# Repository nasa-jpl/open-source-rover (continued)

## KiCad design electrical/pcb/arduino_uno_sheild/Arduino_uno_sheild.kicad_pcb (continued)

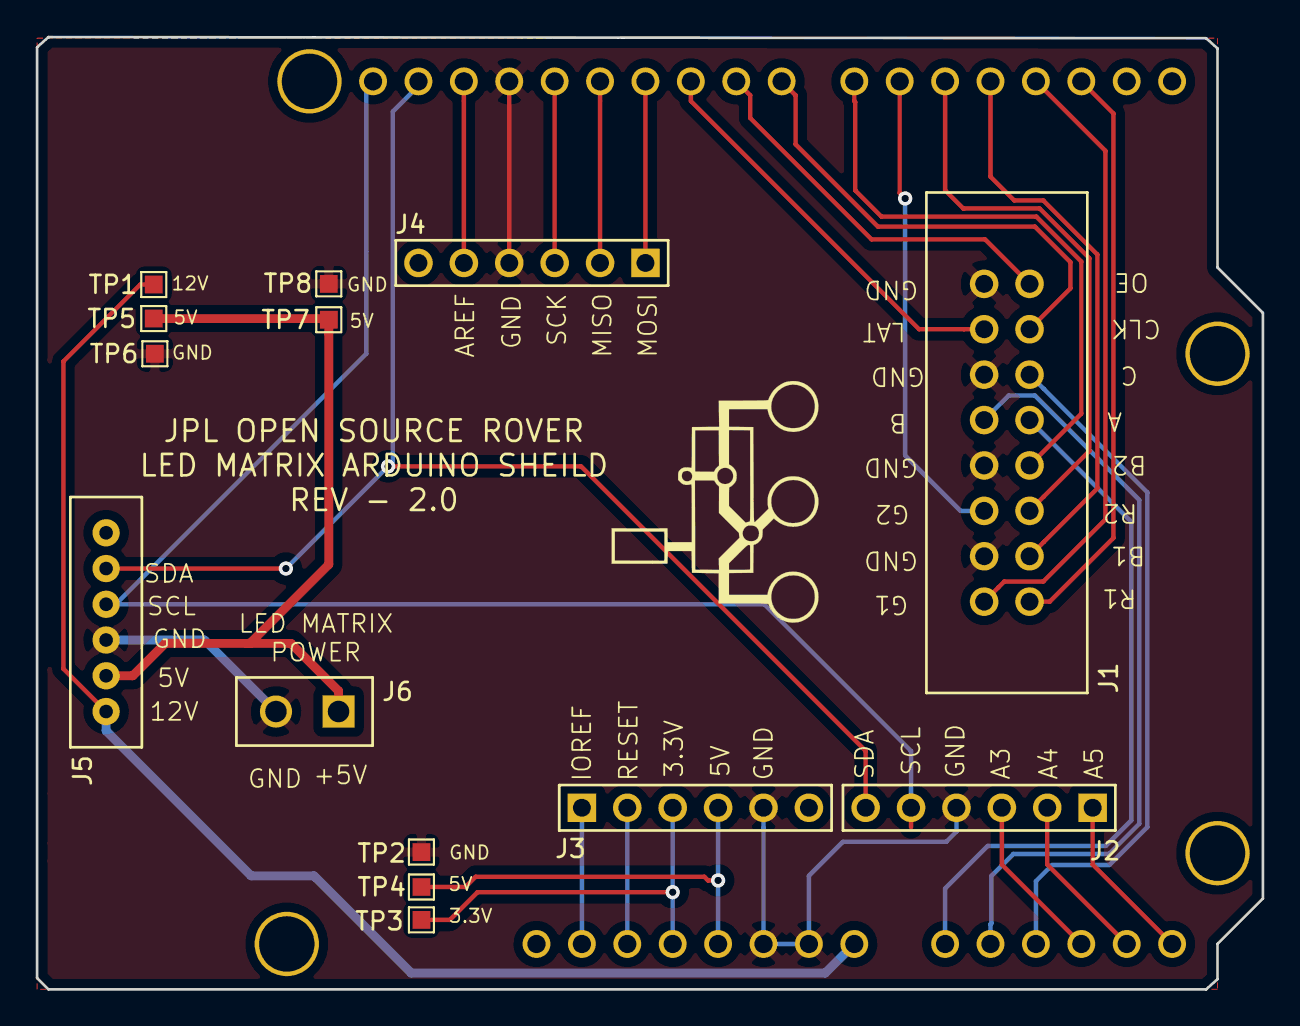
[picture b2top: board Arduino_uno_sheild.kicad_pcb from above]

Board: 2 copper layers, 68.6 x 53.3 mm, 16 parts (0 on the bottom side), 28 nets.

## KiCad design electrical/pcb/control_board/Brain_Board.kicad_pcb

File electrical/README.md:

# Electrical

Please refer to the [PCB assembly](pcb/README.md) and [wiring](wiring/README.md) instructions.

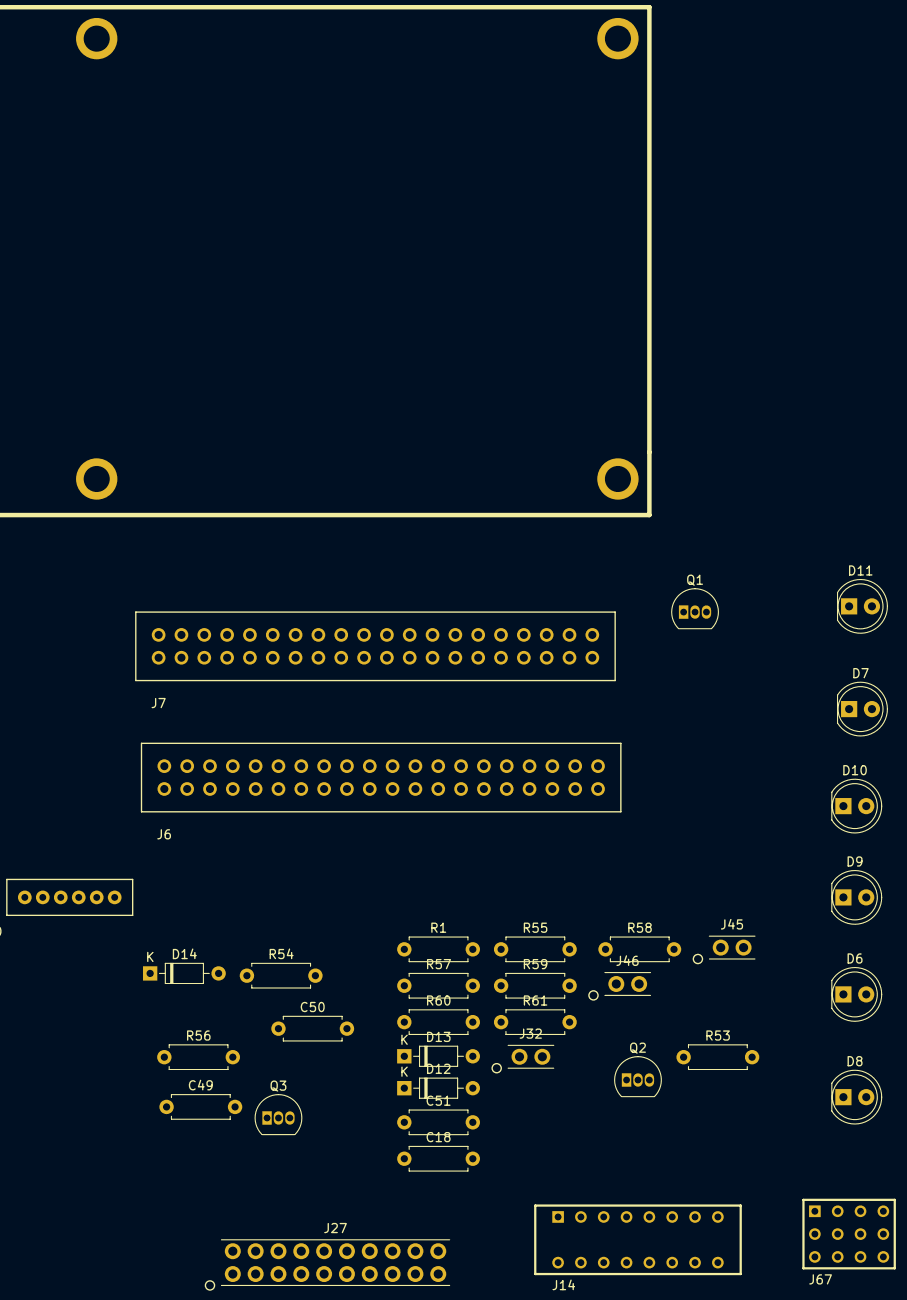
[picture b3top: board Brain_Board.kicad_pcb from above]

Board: 2 copper layers, 36 parts (0 on the bottom side), 28 nets, no tracks yet.

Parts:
C18, C49: 100nf; R_Axial_DIN0207_L6.3mm_D2.5mm_P7.62mm_Horizontal
C50, C51: 10nf; R_Axial_DIN0207_L6.3mm_D2.5mm_P7.62mm_Horizontal
D6, D7, D8, D9, D10, D11: LED - WP1503GT (green); LED_D5.0mm
D12, D13, D14: 1N4148; D_DO-35_SOD27_P7.62mm_Horizontal
J6, J7: S9175-ND_rpi_breakout; S9175-ND
J10: 6posheader; 455-1708-ND
J14: CTS-206-124
J27: PEC10DAAN
J32, J45, J46: PPTC021LFBN-RC
J67: SSW-104-01-F-T
M1: Mounting_Holes; Raspberry pi footprint
Q1, Q2, Q3: 2N3906; TO-92_Inline
R1, R53, R54, R55: 4.7k; R_Axial_DIN0207_L6.3mm_D2.5mm_P7.62mm_Horizontal
R56, R57, R58: 10k; R_Axial_DIN0207_L6.3mm_D2.5mm_P7.62mm_Horizontal
R59, R60, R61: 150; R_Axial_DIN0207_L6.3mm_D2.5mm_P7.62mm_Horizontal

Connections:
+3.3V_brain: C18.1, C50.1, C51.1, J6.1, J6.17, J7.1, J7.17, J14.2, J14.6, J14.10, J27.13, J27.14, Q1.1, Q2.1, Q3.1
+5V_brain: C49.1, J6.2, J6.4, J7.2, J7.4, J10.2, J27.1, J27.2, R1.1
+12V_brain: J10.1, J27.9, J27.10
/Brain Board/E_STOP: J14.1, J14.3, J27.19, R59.2
/Brain Board/E_STOP2: J14.5, J14.7, J27.20, R60.2
/Brain Board/E_STOP2_in: J14.8, J32.1, R54.1
/Brain Board/E_STOP3: J14.9, J14.11, J27.16, R61.2
/Brain Board/E_STOP3_in: J14.12, J45.1, R55.1
/Brain Board/E_STOP_pi: J6.16, J14.4, R53.1
/Brain Board/OEservos: J6.15, J27.18, J46.1
/Brain Board/RXD: D14.1, J6.10, J7.10, J27.4, R1.2
/Brain Board/SCL_rpi: J6.5, J7.5, J10.4, J27.7, J67.2, J67.5, J67.8, J67.11
/Brain Board/SDA_rpi: J6.3, J7.3, J10.5, J27.8, J67.1, J67.4, J67.7, J67.10
/Brain Board/TXD: D13.1, J6.8, J7.8, J27.3
/Brain Board/alert: D12.1, J6.13, J27.17
GND_brain: C18.2, C49.2, D6.1, D7.1, D8.1, D9.1, D10.1, D11.1, J6.6, J6.9, J6.14, J6.20, J6.25, J6.30, J6.34, J6.39, J7.6, J7.9, J7.14, J7.20, J7.25, J7.30, J7.34, J7.39, J10.3, J27.5, J27.6, J32.2, J45.2, J46.2, J67.3, J67.6, J67.9, J67.12, R53.2, R54.2, R55.2
unnamed: C50.2, D13.2, R57.2
unnamed: C51.2, D14.2, R58.2
unnamed: D6.2, R59.1
unnamed: D7.2, R60.1
unnamed: D8.2, R61.1
unnamed: D9.2, Q2.3
unnamed: D10.2, Q3.3
unnamed: D11.2, Q1.3
unnamed: D12.2, R56.2
unnamed: Q1.2, R56.1
unnamed: Q2.2, R57.1
unnamed: Q3.2, R58.1

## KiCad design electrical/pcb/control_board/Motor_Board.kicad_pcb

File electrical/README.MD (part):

<!--[title](Pictures/Electronics/electronics title.png)
-->
# Open Source Rover: Electrical Assembly Instructions
Authors: Michael Cox, Eric Junkins, Olivia Lofaro

Reference herein to any specific commercial product, process, or service by trade name, trademark, manufacturer, or otherwise, does not constitute or imply its endorsement by the United States Government or the Jet Propulsion Laboratory, California Institute of Technology.

Copyright 2018 California Institute of Technology. Government sponsorship acknowledged

# 1. Overview
First, it is important to examine the components we will use in the rover and understand how both data and power travel through the system. Figure 1 shows how each of the electrical components and boards receives power, and Figure 2 shows how data are sent from each of the electrical systems and what communication protocol it uses.

**Figure 1. Electrical Power Overview**

One important thing to note from the above is that there are multiple different voltages in the system. There is the unregulated voltage coming from the battery, 5V regulated coming from the voltage regulator, and the 12V motor voltage which is sent from the motor controllers to the motors.

  **Figure 2. Electrical Data Overview**

For the data transmission, we use both 3.3V and 5V digital logic systems, analog signals (of varying max voltages), and serial communication between devices. Information on these protocols can be found at:

* [Serial Communications](https://en.wikipedia.org/wiki/Serial communication)
* [Analog vs. Digital](https://learn.sparkfun.com/tutorials/analog-vs-digital)

**Table 1. Electrical Components**

Part | Description
---- | -----------
Battery | Provides power to the system. Has an unregulated voltage range of around 11.5V - 16.75V depending on its charge level
Switch | Mechanical disconnect of the electrical power to the rest of the robot
Volt Meter | Monitors and displays information such as current draw, voltage level, and power consumption of the robot
Voltage Regulator | Takes in the unregulated battery voltage and outputs a steady regulated voltage for consumption by electronics.
Raspberry Pi 3 | Acts as the brains and processing power of the robot
Arduino Uno | Runs the LED Matrix
LED Matrix | Gives the robot a display and a personality
Motor Controllers | Sends voltage signals to the motors telling the motors the direction and speed at which to spin. Reads encoder data
Encoders | Monitors the position of the motor to give information about speed and position
Control Board PCB | Custom Printed Circuit Board to manage power and data transmition between electronics components.

## 1.1. Tools Necessary

**Table 2. Necessary Tools**

Part | Image
---- | -----
Heat Shrink Gun |
Digital Mutimeter |
Soldering Iron |
Solder |
Solder Wick |
Power Supply (optional) |

This project assumes you have the tools shown in Figure 3. These will all be used in the construction and testing/debugging of this project. Most of these can be purchased inexpensively though DigiKey, Amazon, or other retailers.

## 1.2. Component Descriptions
The following are brief descriptions and basic notes about some of the components we use in this project. For more detailed information on each component, consult the data sheet for that component.
### 1.2.1 Battery
The battery is used to power all the electrical components and the motors in our rover. The biggest driving factor for battery selection was safety of the battery chemistry while still being able to drive the current and voltage necessary for operation of all the electronics (we’ll go into these requirements more later). The recommended battery was chosen because of its Poly Switch and PCB protection. These limit the amount of current that can be pulled from the battery, as well as give protection against things like electrical shorts and overcharging/fully discharging the battery.
### 1.2.2. Voltage Regulators
As our battery outputs unregulated voltage based on its charge level, voltage regulators are added to give steady DC power to the electronic components. There is a 5V regulator that runs the raspberry pi and the LED matrix, and a 12V regulator that supplies power to the Arduino Uno.
### 1.2.3. Raspberry Pi 3
We selected the Raspberry Pi 3 Model B as the ”brain” of the rover. We chose the Pi because it allows users at many levels of programming knowledge to gain familiarity in basic programming concepts without a complicated learning curve. It is also widely used in the maker community, so modifications and additions on the base rover should be easy. The Pi 3 also comes with WiFi and bluetooth modules built into the board and we therefore don’t need additional dongles to communicate over WiFi or bluetooth. This retains all 4 USB ports for addons and modifications to the project.
### 1.2.4. Arduino Uno
An Arduino Uno runs the LED matrix. The matrix is controlled by a set of GPIO pins from the Arduino and is multiplexed such that these few pins can control all the LEDs. Arduino is designed for these kinds of applications where very high frequency switching of GPIO pins are necessary. The Uno is better suited for this than the RPi, and offloads some compute power so that the Pi has more capacity to run rover software.

### 1.2.5. Control Board PCB
The custom Printed Circuit Board is designed to help manage the power distribution and data signals for the rover. It takes in battery power, splits it up to each of the voltage regulators and motor controllers which in turn power each of the individual electronics on the robot. It also takes in encoders from the motors and distributes them to the motor controllers, and provides serial UART communication between the RPi and the Motor controllers as well as the Arduino Uno. The first version of the Open Source Rover required you to run each of these wires by hand; the custom Control Board does much of the routing for you.
### 1.2.6. LED Matrix
The LED Matrix is a 16x32 pixel display that is controlled by the Arduino Uno. The LED matrix is controllable via software and can be programmed to display anything you like.
### 1.2.7. Motors
Motors cause the actual movement of the robot. There are many types of motors; in this project we will be used brushed DC motors. More information on different types of motors and a link about how brushed DC motors work can be found at the following links:

* [Brushed DC Motors](https://en.wikipedia.org/wiki/Brushed DC electric motor) 
* [Electric Motors](https://en.wikipedia.org/wiki/Electric motor)

### 1.2.8. Encoders
Encoders give us readings on the position and speed of motors as they spin. There are two types of encoders in this project: absolute and quadrature. An absolute encoder is used to get the position of the motor on a fixed scale such that you always know the absolute position of the motor even after power cycling the system. Absolute encoders will usually have one output, which will either be a PWM digital signal or an analog signal. Each of these signals will have a specific reading corresponding to where the motor currently is on the fixed position scale. Absolute encoders are typically more expensive than their quadrature encoder counterparts, which will sense position only relative to the last time the power was cycled or the signal was reset. Quadrature encoders use two digital signals and look at the difference between the signals to sense movement. More information about quadrature encoders can be found at:

* [Quadrature Encoder Basics](http://www.dynapar.com/Technology/Encoder Basics/Quadrature Encoder/)

In this project, we use absolute encoders on the corner wheels to get absolute measurements on where the corner wheels are turned/pointed. We use quadrature encoders at each of the driving wheels to get speed measurements.
# 2. Powering Components
This section will go through the process of powering each of the components from the battery. During this project you will need to cut, strip, and solder wires to extend and split electrical connections. It is important to understand how to do this safely so that you are protecting your system from electrical shorts. Below are a few quick links on these skills, however it is crucial that you fully understand these processes before proceeding.

* [SparkFun Stripping Wire](https://learn.sparkfun.com/tutorials/working-with-wire/how-to-strip-a-wire) 
* [Splicing Wire](https://www.wikihow.com/Splice-Wire)
* [YouTube Making Connections](https://www.youtube.com/watch?v=Y8wjv6lj5KU)

**Note** Please read through this entire section and understand it fully before starting to connect devices and electronics together.

## 2.1. Switch, Volt Meter, and Control Board
There are a couple of very important things to be aware of as you are making these connections, as with any project where you are working with batteries or electrical current:
**THE BATTERY IS LIVE AT ALL TIMES.** This means that at any point, if the two terminals of the battery come in contact they will cause an electrical short which could be very dangerous. This may trigger the protection circuit in the battery that we chose and prevent extensive damage, but we do not want to rely on that for safety. Make sure to keep the battery terminals of the +V and GND separated at all times with no possibility of contact.

The battery connectors will only fit together one way. That means you have to make sure your connections are correct the first time when soldering them in: make sure to verify this before connecting anything to the battery.
The switch we use is a Single Pole - Single Throw switch. This means that either the two terminals are connected together in one switch position or there is a physical disconnect when the switch is in the other position. Make sure to test the switch and know which are its **ON** and **OFF** positions previous to connecting it to anything. An easy way to test the switch is to use the ’Diode’ setting on your Digital Multimeter (DMM).
It is extremely important to plug the battery in the correct direction into the volt meter as well, as plugging it in backwards (even for an instant) could damage or destroy the volt meter.

Using the Tamiya connectors, connect the battery to the switch and then the volt meter according to Figure 4. The Tamiya connectors allow you to disconnect the battery from the rest of the system so you can recharge the battery.

**Table 3. Necessary Parts**

Item | Ref | Qty | Image 
---- | --- | --- | ----- 
Battery | E36 | 1 | 
16 AWG Wire (Black) | X2 | 1 |  
16 AWG Wire (Red) | X1 | 1 |   
Battery Charger | E41 | 1 |  
Tamiya Connectors| E35 | 1 | 

**Figure 4. Connecting the Battery to switch and board**
 
# 3. Connecting Data Cables
**NOTE**: Before proceeding, you need to have completed the assembly of the custom PCB board and populated all the components. If you have not yet done so, build the Control Board now by following the document at /Electrical/PCB Assembly.pdf.

Next, we will next plug in all the cables that allow the various devices to communicate with each other.

**Table 4. Necessary Parts**

Item | Ref | Qty | Image 
---- | --- | --- | ----- 
Rectangular 6P 1x6 Jumper Cable | E26 | 1 | 
USB Power Cable | E28 | 1| 
Rectangular 40P 2x20 Ribbon Cable | E29 | 1 | 
Rectangular 16P Ribbon Cable | E30 | 1| 
 USB to TTL Serial Adapter | E48 | 1| 

1. Connect the E26 cable from the J10 Connector on the Control Board to the J5 Connector on the Arduino Shield
1. Connect the E30 16 Position ribbon cable from the J1 Connector to the INPUT Connector on the LED Matrix
1. Connect the E48 TTL serial to USB cable from any USB port on the Raspberry Pi to the 6 Position headers at J8. The pinout should match the table below (see Figure 5):

**Table 5. J8 Pins and Wire Colors**

Control Board PCB J8 pin | TTL Serial cable wire color
------------------------ | ---------------------------
1. GND | Black
2. N/A | Not Connected
3. 5V | Red
4. TxD | Green
5. RxD | White
6. N/A | Not Connected

  **Figure 5. USB / TTL Serial Cable Connection**
  
# 4. Connecting Motors and Encoders
Next, we will connect the motors and encoders to the RoboClaw motor controllers. For each of the 10 motors you will need to connect motor power as well as the encoders. This means that there will be close to 60 wires traveling between the motor controllers and the motors/encoders, so it is very important to try to keep your wires organized and bundled together well. Below is some information about strain relief and using wire braid in your electronics systems. See these links and Figures 6 and 7 for examples.

* [Techopedia Strain Relief](https://www.techopedia.com/definition/2301/strain-relief) 
* [YouTube Wire Braid](https://www.youtube.com/watch?v=FeCs98TSsYQ)

**Figure 6. Motor Wire Routing**
    
An example of how we routed our wiring is shown by Figure 6. It is important to give strain relief in the cable as you are routing it through, as well as to give extra wiring for the locations that can move. In addition, Figure 7 shows how we routed the wires through the rocker-bogie, and then from the rocker-bogie into the main body. Try to pick locations that reduce strain on the wires as the robot legs move when you are routing wires into the body.

**Figure 7. Serial signal routing**

**Table 6. Necessary Parts**

Item | Ref | Qty | Image
---- | --- | --- | ----- 
20AWG Wire (Black) | X2 | N/A |  
20AWG Wire (Red) | X1 | N/A |  
30AWG Wire (White) | X3 | N/A |  
30AWG Wire (Blue) | X4 | N/A |  
30AWG Wire (Yellow) | X5 | N/A |  
30AWG Wire (Green) | X6 | N/A |  
3 Pin Micro Connector | E40 | 4 | 
Wire Braid | E42 | N/A | 
Heat Shrink Tubing | E44 | 1 | 

The below table and figure shows an approximate amount of length of wire you will need to reach each of the motors, based on how we think is best to route the wiring through the suspension system. Cut these lengths and strip both ends of the wires.
   
**Table 7. Wire Lengths by Section**

Section | Wires Needed | Length [inches]
------- | ------------ | --------------- 
A | 2x | 20AWG & 4x 30AWG | 35
B | 2x | 20AWG & 4x 30AWG | 28
C | 2x | 20AWG & 4x 30AWG | 48
D | 2x | 20AWG & 3x 30AWG | 20
E | 2x | 20AWG & 3x 30AWG | 32

  **Figure 8. Wire lengths**
  
## 4.1. Drive Motors
We will begin with the drive motors (the 6 motors that are directly connected to each drive wheel). Make sure to look at which RoboClaw corresponds to which motors that that RoboClaw controls. It is important that this ordering is preserved. Figure 9 shows the motor pinout for the motors for the drive system. You will be wiring each of these to the terminal blocks on the control board. One method of doing this is to cut off the 6 pin connector from the motor and solder directly to the wires there. Another way is to add your own connector if you wish to be able to change the motor out easier in the future.

  Figure 9: RoboClaw - Motor Assignments
  
The terminal blocks that correspond to the drive motors are connectors J17-J22. You will see them labeled on the control board corresponding to which motor it should connect to1.
Each of the terminal blocks are identical for the drive motors; pay attention to the silkscreen to know which screw terminal to plug the wire into. The terminal block position on the board will correspond roughly with which motor it goes to on the robot, ie. the J17 connector is in the front-right of the
board when installed in the robot, and connects to the front-right drive wheel.

Control Board Label | Motor Wire Color | Signal
------------------- | ---------------- | ------
Mx+ | Red | Motor+
Mx- | Black | Motor-
GND + | Green | Ground
5V | Blue | Encoder Power
ENxA | Yellow | Encoder signal A
ENxB | White | Encoder signal B

## 4.2. Corner Motors/Encoders
The big difference between the corner motors and drive motors is that the corners use absolute encoders. The absolute encoders are separate from the motor and so we have to do a little bit of work to get them to interface with the motor controllers. The corner motors only have the two connections to the physical motor: the (+) and (-) going to the top of the motor. However, you must also hook up the absolute encoder. When plugged into the encoder, the 3-pin Micro connector will have 3 wires coming out of it, shown in Figure 10.

*Make sure you are using a REV-E or newer board. There was an initial release of board files that had the silkscreen reversed from left-right for all motors (drive and corner). If you have a REV-D or earlier board, the silkscreen may have these labels backwards.*

  **Figure 10. 3-pin Micro connector**
 
Pin | Description | Color
--- | ----------- | -----
1 | +5V DC Power | Orange
2 | 0-5V Analog | Blue
3 | Ground | Brown

Similar to the drive motors, connect each of the corner motors and encoders to its corresponding terminal block (J23-26 on the control board). Below is the pinout for how to connect the encoders: 

**Note:** **These are NOT the same color and pinout as the drive motors!**

Control Board Label | Motor Wire Color | Signal
------------------- | ---------------- | ------
Mx+ | Red | Motor+
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
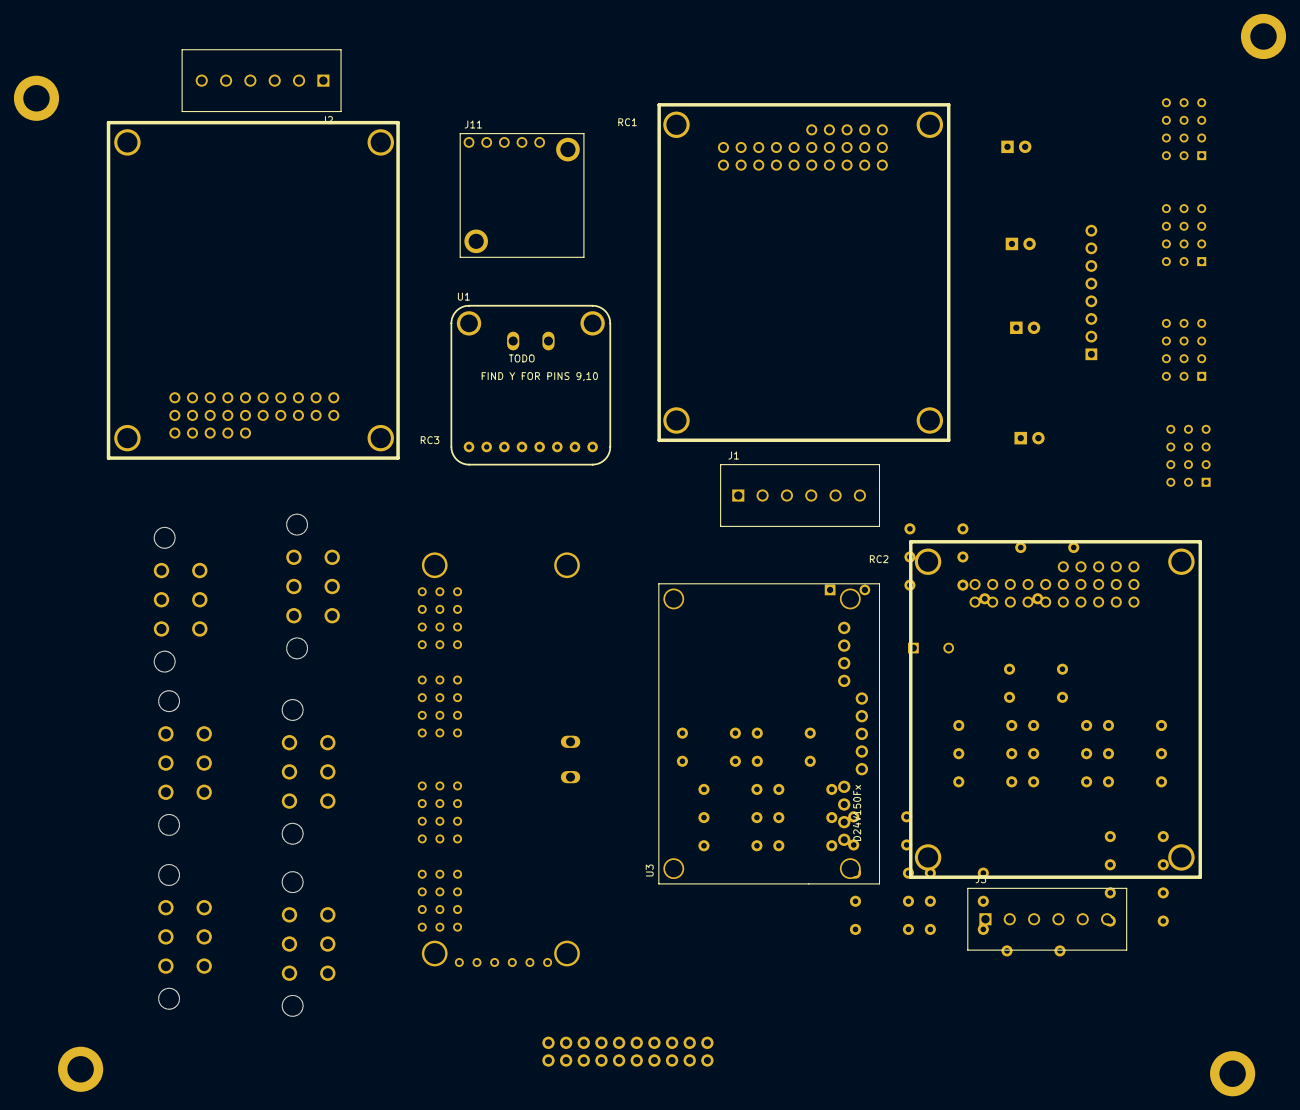
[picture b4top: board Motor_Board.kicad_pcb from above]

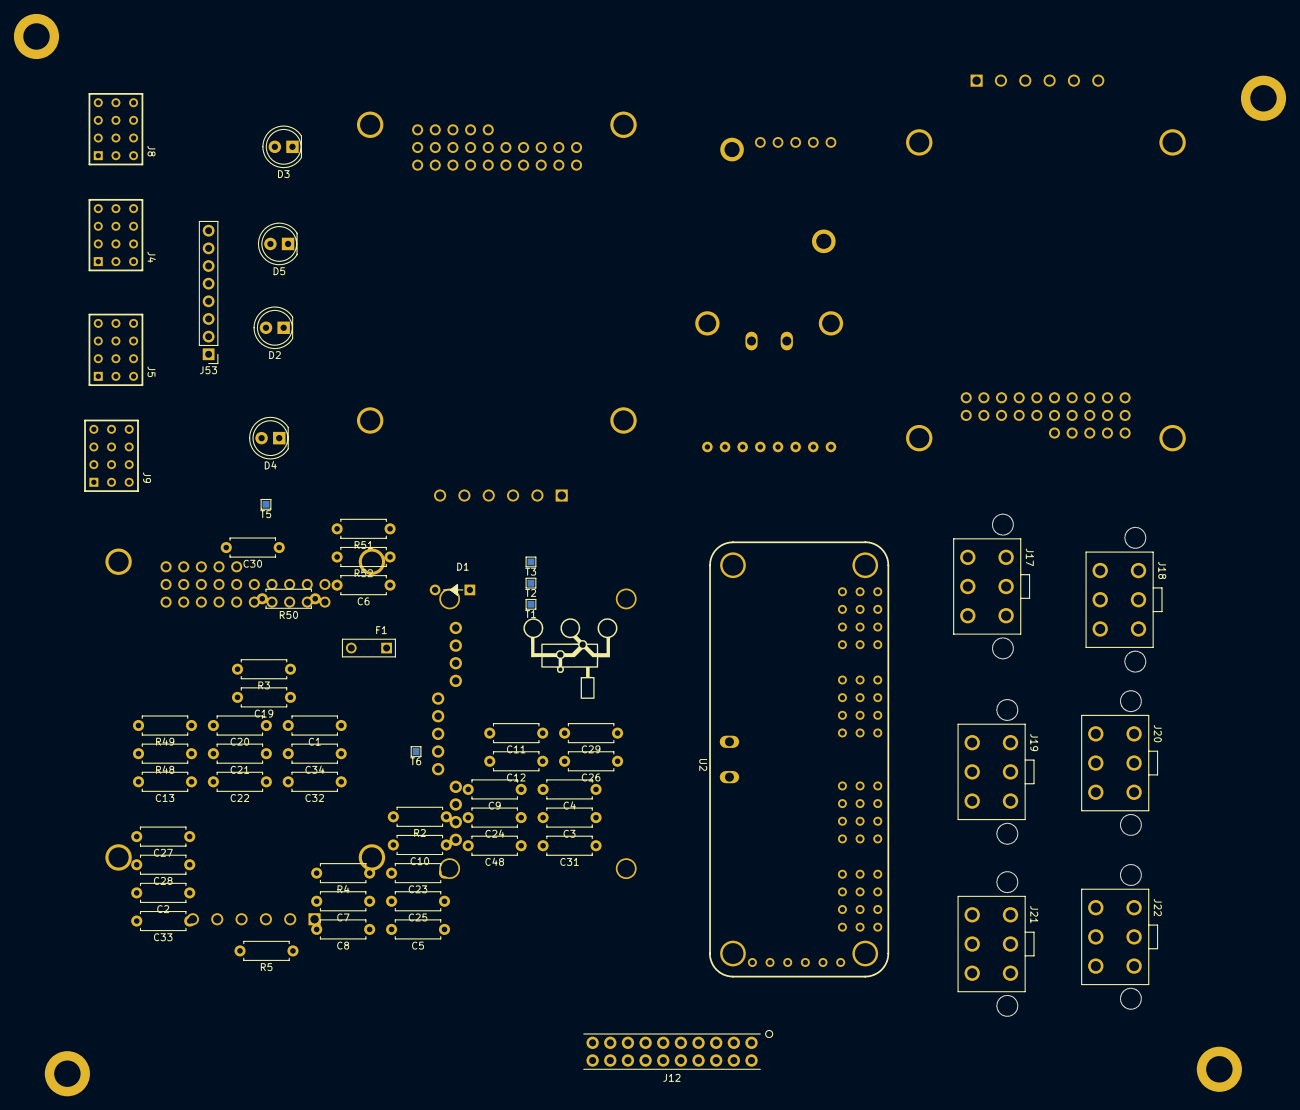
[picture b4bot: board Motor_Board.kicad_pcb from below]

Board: 2 copper layers, 77 parts (71 on the bottom side), 62 nets, no tracks yet.

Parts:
C1, C2, C3, C4, C5, C6, C7, C48: 100nf; R_Axial_DIN0207_L6.3mm_D2.5mm_P7.62mm_Horizontal
C8, C9, C10, C11, C12, C13, C31, C32, C33, C34: 100uf; R_Axial_DIN0207_L6.3mm_D2.5mm_P7.62mm_Horizontal
C19, C20, C21, C22, C23, C24, C25, C26, C27, C28, C29, C30: 10nf; R_Axial_DIN0207_L6.3mm_D2.5mm_P7.62mm_Horizontal
D1: D; 497-2738-5-ND
D2, D3, D4, D5: LED - WP1503GT (green); LED_D5.0mm
F1: Fuse; 507-1937-1-ND
J1, J2, J3: ED2627-ND
J4, J5, J8, J9: TSW-104-07-F-T; TSW-104-07-FT
J11: S7038-ND_regulator_D24V22F12; D24V22F12 Regulator
J12: PPTC102LFBN-RC
J17, J18, J19, J20, J21, J22: Molex_172675-0613
J53: PEC08SAAN; PinHeader_1x08_P2.54mm_Vertical
MH1, MH2, MH3, MH4: #6THRU-HOLE
R2: 10k; R_Axial_DIN0207_L6.3mm_D2.5mm_P7.62mm_Horizontal
R3, R4, R5, R48: 4.7k; R_Axial_DIN0207_L6.3mm_D2.5mm_P7.62mm_Horizontal
R49, R50: 680; R_Axial_DIN0207_L6.3mm_D2.5mm_P7.62mm_Horizontal
R51: 470; R_Axial_DIN0207_L6.3mm_D2.5mm_P7.62mm_Horizontal
R52: 150; R_Axial_DIN0207_L6.3mm_D2.5mm_P7.62mm_Horizontal
RC1, RC2, RC3: RoboClaw; Roboclaw Mount
T1, T2, T3, T5, T6: test_point; TestPoint_Pad_1.0x1.0mm
U1: INA260
U2: PCA9685; PCA9685 Servo Controller
U3: D24V150Fx
y1: rover_silkscreen; rover_image

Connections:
+3.3V_motor: C1.1, C48.2, J12.13, J12.14, R3.2, R4.2, R5.2, U1.1, U2.2
+5V_motor: C2.1, C3.1, C4.1, C5.1, C6.1, C7.1, C8.2, C9.2, C10.2, C11.2, C12.2, C13.2, C31.2, C32.2, C33.2, C34.2, J4.2, J4.5, J4.8, J4.11, J5.2, J5.5, J5.8, J5.11, J8.2, J8.5, J8.8, J8.11, J9.2, J9.5, J9.8, J9.11, J12.1, J12.2, J17.4, J18.4, J19.4, J20.4, J21.4, J22.4, J53.1, R52.2, U3.12, U3.13
+12V_motor: J11.5, J12.9, J12.10, J53.2, R51.2, T5.1
+BATT: J1.3, J2.3, J3.3, J11.3, R50.2, T3.1, U1.10, U2.7, U3.1, U3.2
/Motor Board/BATTPOS: D1.1, F1.1, R49.2
/Motor Board/E_STOP: J12.19, R3.1, RC1.23, RC2.23, RC3.23
/Motor Board/E_STOP2: J12.20, R4.1, RC1.24, RC2.24, RC3.24
/Motor Board/E_STOP3: J12.16, R5.1, RC1.25, RC2.25, RC3.25
/Motor Board/OEservos: J12.18, U2.5
/Motor Board/RC1EN1A: C19.1, J17.5, RC1.7
/Motor Board/RC1EN1B: C20.1, J17.6, RC1.8
/Motor Board/RC1EN2A: C21.1, J18.5, RC1.9
/Motor Board/RC1EN2B: C22.1, J18.6, RC1.10
/Motor Board/RC1M1A: J1.1, J17.1
/Motor Board/RC1M1B: J1.2, J17.2
/Motor Board/RC1M2A: J1.5, J18.1
/Motor Board/RC1M2B: J1.6, J18.2
/Motor Board/RC2EN1A: C23.1, J19.5, RC2.7
/Motor Board/RC2EN1B: C24.1, J19.6, RC2.8
/Motor Board/RC2EN2A: C25.1, J20.5, RC2.9
/Motor Board/RC2EN2B: C26.1, J20.6, RC2.10
/Motor Board/RC2M1A: J2.1, J19.1
/Motor Board/RC2M1B: J2.2, J19.2
/Motor Board/RC2M2A: J2.5, J20.1
/Motor Board/RC2M2B: J2.6, J20.2
/Motor Board/RC3EN1A: C27.1, J21.5, RC3.7
/Motor Board/RC3EN1B: C28.1, J21.6, RC3.8
/Motor Board/RC3EN2A: C29.1, J22.5, RC3.9
/Motor Board/RC3EN2B: C30.1, J22.6, RC3.10
/Motor Board/RC3M1A: J3.1, J21.1
/Motor Board/RC3M1B: J3.2, J21.2
/Motor Board/RC3M2A: J3.5, J22.1
/Motor Board/RC3M2B: J3.6, J22.2
/Motor Board/RXD: J12.4, J53.5, RC1.22, RC2.22, RC3.22
/Motor Board/SCL_rpi: J12.7, J53.6, U1.3, U2.4
/Motor Board/SDA_rpi: J12.8, J53.7, U1.4, U2.3
/Motor Board/SWIN: D1.2, F1.2, R2.1
/Motor Board/TXD: J12.3, J53.4, RC1.21, RC2.21, RC3.21
/Motor Board/alert: J12.17, R48.2, U1.5
/Motor Board/servo_pwm_ch0: J9.1, U2.9
/Motor Board/servo_pwm_ch1: J9.4, U2.12, U2.15
/Motor Board/servo_pwm_ch3: J9.10, U2.18
/Motor Board/servo_pwm_ch4: J4.1, U2.21
/Motor Board/servo_pwm_ch5: J4.4, U2.24
/Motor Board/servo_pwm_ch6: J4.7, U2.27
/Motor Board/servo_pwm_ch7: J4.10, U2.30
/Motor Board/servo_pwm_ch8: J5.1, U2.33
/Motor Board/servo_pwm_ch9: J5.4, U2.36
/Motor Board/servo_pwm_ch10: J5.7, U2.39
/Motor Board/servo_pwm_ch11: J5.10, U2.42
/Motor Board/servo_pwm_ch12: J8.1, U2.45
/Motor Board/servo_pwm_ch13: J8.4, U2.48
/Motor Board/servo_pwm_ch14: J8.7, U2.51
/Motor Board/servo_pwm_ch15: J8.10, U2.54
GND_motor: C1.2, C2.2, C3.2, C4.2, C5.2, C6.2, C7.2, C8.1, C9.1, C10.1, C11.1, C12.1, C13.1, C19.2, C20.2, C21.2, C22.2, C23.2, C24.2, C25.2, C26.2, C27.2, C28.2, C29.2, C30.2, C31.1, C32.1, C33.1, C34.1, C48.1, D2.1, D3.1, D4.1, D5.1, J1.4, J2.4, J3.4, J4.3, J4.6, J4.9, J4.12, J5.3, J5.6, J5.9, J5.12, J8.3, J8.6, J8.9, J8.12, J9.3, J9.6, J9.9, J9.12, J11.4, J12.5, J12.6, J17.3, J18.3, J19.3, J20.3, J21.3, J22.3, J53.3, R48.1, T2.1, T6.1, U1.2, U2.6, U2.8, U3.3, U3.4, U3.10, U3.11
unnamed: D2.2, R49.1
unnamed: D3.2, R50.1
unnamed: D4.2, R51.1
unnamed: D5.2, R52.1
unnamed: R2.2, U1.9
unnamed: U2.10, U2.13, U2.16, U2.19, U2.22, U2.25, U2.28, U2.31, U2.34, U2.37, U2.40, U2.43, U2.46, U2.49, U2.52, U2.55
unnamed: U2.11, U2.14, U2.17, U2.20, U2.23, U2.26, U2.29, U2.32, U2.35, U2.38, U2.41, U2.44, U2.47, U2.50, U2.53, U2.56

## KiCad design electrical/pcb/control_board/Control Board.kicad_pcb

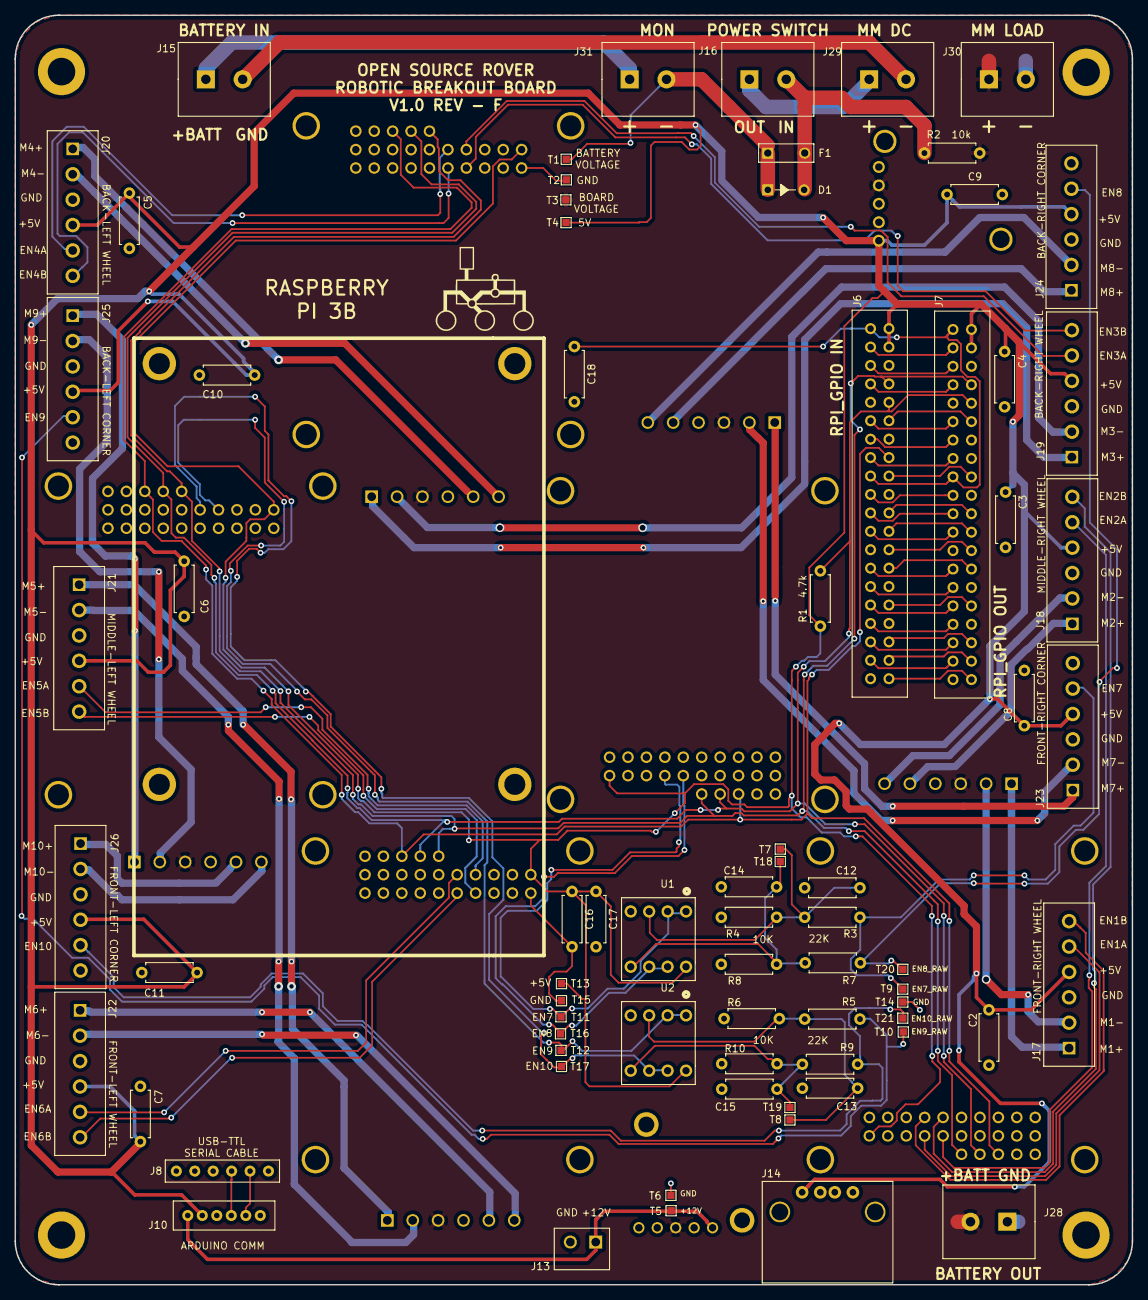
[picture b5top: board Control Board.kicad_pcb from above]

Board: 2 copper layers, 154.0 x 175.0 mm, 92 parts (0 on the bottom side), 84 nets.

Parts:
C2, C3, C4, C5, C6, C7, C8, C9, C10, C11, C16, C17, C18: 100nf; R_Axial_DIN0207_L6.3mm_D2.5mm_P7.62mm_Horizontal
C12, C13, C14, C15: 100nF; R_Axial_DIN0207_L6.3mm_D2.5mm_P7.62mm_Horizontal
D1: D; 497-2738-5-ND
F1: Fuse; 507-1937-1-ND
J1, J2, J3, J4, J5: ED2627-ND
J6, J7: S9175-ND
J8: 6posheader; 6x1 Header Pin 0.1 Pitch
J9: S7038-ND
J10: 6posheader; 455-1708-ND
J11: S7038-ND; D24V22F12 Regulator
J13: ED1501-ND
J14: ED2989-ND-USB; ED2989-ND USB Conn
J15, J16, J28, J29, J30, J31: ED2580-ND
J17, J18, J19, J20, J21, J22, J23, J24, J25, J26: ED2744-ND
M1: Mounting_Holes; Raspberry pi footprint
MH1, MH2, MH3, MH4: #6THRU-HOLE
R1: 4.7K; R_Axial_DIN0207_L6.3mm_D2.5mm_P7.62mm_Horizontal
R2, R4, R6, R8, R10: 10K; R_Axial_DIN0207_L6.3mm_D2.5mm_P7.62mm_Horizontal
R3, R5, R7, R9: 22K; R_Axial_DIN0207_L6.3mm_D2.5mm_P7.62mm_Horizontal
RC1, RC2, RC3, RC4, RC5: RoboClaw; Roboclaw Mount
T1, T2, T3, T4, T5, T6, T7, T8, T9, T10, T11, T12, T13, T14, T15, T16, T17, T18, T19, T20, T21: test_point; TestPoint_Pad_1.0x1.0mm
U1, U2: LM358-N; AE9986-ND
y1: rover_silkscreen; rover_image

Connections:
+5V: C2.1, C3.1, C4.1, C5.1, C6.1, C7.1, C8.1, C9.1, C10.1, C11.1, C16.1, C17.1, J6.2, J6.4, J7.2, J7.4, J9.5, J10.2, J14.1, J17.4, J18.4, J19.4, J20.4, J21.4, J22.4, J23.4, J24.4, J25.4, J26.4, R1.2, RC1.1, RC2.1, RC3.1, RC4.1, RC5.1, T4.1, T13.1, U1.8, U2.8
+12V: J10.1, J11.5, J13.1, T5.1
+BATT: J1.3, J2.3, J3.3, J4.3, J5.3, J9.2, J11.3, J28.2, J30.1, R2.2, T3.1
/3.3V: C18.1, J6.1, J6.17, J7.1, J7.17
/BATTNEG: J15.2, J29.2
/BATTPOS: J15.1, J31.1
/E_STOP: J6.16, RC1.23, RC2.23, RC3.23, RC4.23, RC5.23
/GPIO05: J6.29, J7.29
/GPIO06: J6.31, J7.31
/GPIO12: J6.32, J7.32
/GPIO13: J6.33, J7.33
/GPIO16: J6.36, J7.36
/GPIO19: J6.35, J7.35
/GPIO20: J6.38, J7.38
/GPIO21: J6.40, J7.40
/GPIO26: J6.37, J7.37
/GPIO_CLK: J6.7, J7.7
/GPIO_GEN0: J6.11, J7.11
/GPIO_GEN1: J6.12, J7.12
/GPIO_GEN2: J6.13, J7.13
/GPIO_GEN3: J6.15, J7.15
/GPIO_GEN5: J6.18, J7.18
/GPIO_GEN6: J6.22, J7.22
/GPI_CE1_N: J6.26, J7.26
/I2C_ID1: J6.27, J7.27
/I2C_ID2: J6.28, J7.28
/MMDC+: J16.1, J29.1
/RC1EN1A: J17.5, RC1.7
/RC1EN1B: J17.6, RC1.8
/RC1EN2A: J18.5, RC1.9
/RC1EN2B: J18.6, RC1.10
/RC1M1A: J1.1, J17.1
/RC1M1B: J1.2, J17.2
/RC1M2A: J1.5, J18.1
/RC1M2B: J1.6, J18.2
/RC2EN1A: J19.5, RC2.7
/RC2EN1B: J19.6, RC2.8
/RC2EN2A: J20.5, RC2.9
/RC2EN2B: J20.6, RC2.10
/RC2M1A: J2.1, J19.1
/RC2M1B: J2.2, J19.2
/RC2M2A: J2.5, J20.1
/RC2M2B: J2.6, J20.2
/RC3EN1A: J21.5, RC3.7
/RC3EN1B: J21.6, RC3.8
/RC3EN2A: J22.5, RC3.9
/RC3EN2B: J22.6, RC3.10
/RC3M1A: J3.1, J21.1
/RC3M1B: J3.2, J21.2
/RC3M2A: J3.5, J22.1
/RC3M2B: J3.6, J22.2
/RC4EN1A: RC4.7, T11.1, U1.1, U1.2
/RC4EN1A_RAW: J23.5, R3.1, T9.1
/RC4EN2A: RC4.9, T16.1, U1.6, U1.7
/RC4EN2A_RAW: J24.5, R7.1, T20.1
/RC4M1A: J4.1, J23.1
/RC4M1B: J4.2, J23.2
/RC4M2A: J4.5, J24.1
/RC4M2B: J4.6, J24.2
/RC5EN1A: RC5.7, T12.1, U2.1, U2.2
/RC5EN1A_RAW: J25.5, R5.1, T10.1
/RC5EN2A: RC5.9, T17.1, U2.6, U2.7
/RC5EN2A_RAW: J26.5, R9.1, T21.1
/RC5M1A: J5.1, J25.1
/RC5M1B: J5.2, J25.2
/RC5M2A: J5.5, J26.1
/RC5M2B: J5.6, J26.2
/RXD: J6.10, J7.10, R1.1, RC1.22, RC2.22, RC3.22, RC4.22, RC5.22
/SCL1: J6.5, J7.5
/SDA1: J6.3, J7.3
/SPI_CEO_N: J6.24, J7.24
/SPI_CLK: J6.23, J7.23
/SPI_MISO: J6.21, J7.21
/SPI_MOSI: J6.19, J7.19
/SWIN: D1.2, F1.2, J16.2, R2.1
/TTL_RXD: J8.5, J10.5
/TTL_TXD: J8.4, J10.4
/TXD: J6.8, J7.8, RC1.21, RC2.21, RC3.21, RC4.21, RC5.21
GND: C2.2, C3.2, C4.2, C5.2, C6.2, C7.2, C8.2, C9.2, C10.2, C11.2, C12.1, C13.1, C14.1, C15.1, C16.2, C17.2, C18.2, J1.4, J2.4, J3.4, J4.4, J5.4, J6.6, J6.9, J6.14, J6.20, J6.25, J6.30, J6.34, J6.39, J7.6, J7.9, J7.14, J7.20, J7.25, J7.30, J7.34, J7.39, J8.1, J9.3, J9.4, J10.3, J11.4, J13.2, J14.4, J17.3, J18.3, J19.3, J20.3, J21.3, J22.3, J23.3, J24.3, J25.3, J26.3, J28.1, J30.2, R4.2, R6.2, R8.2, R10.2, RC1.2, RC2.2, RC3.2, RC4.2, RC5.2, T2.1, T6.1, T15.1, U1.4, U2.4
unnamed: C12.2, R3.2, R4.1, T7.1, U1.3
unnamed: C13.2, R5.2, R6.1, T8.1, U2.3
unnamed: C14.2, R7.2, R8.1, T18.1, U1.5
unnamed: C15.2, R9.2, R10.1, T19.1, U2.5
unnamed: D1.1, F1.1, J31.2, T1.1

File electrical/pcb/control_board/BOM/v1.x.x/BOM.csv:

References,Qty,Description,Manufacturer,MPN,Digikey,Mouser,RS,Newark,Farnell
"C1, C12, C13, C14, C15, C17, C3, C5, C4, C2, C10, C9, C8, C7, C6, C11, C16",17,100nF axial,KEMET,C410C104M5U5TA7200,399-4454-1-ND,80C410C104M5UTR,,,1650914
D1,1,Power Diode,STMicroelectronics,STPS10L25D,497-2738-5-ND,511STPS10L25D,7958795,,9803360
F1,1,10A Fuse,Bel Fuse,0697H9100-01,507-1916-ND,5300697H910001,,,
J10,1,Connector Header pin 6P 6x1,JST,B6B-PH-K-S(LF)(SN),455-1708-ND,,8201447,,9492453
J13,1,Term block 2p side entry (3.5mm),On Shore Technology,ED550/2DS,ED1501-ND,,,,
"J14, J12",2,USB Conn ED2989-ND-USB,On Shore Technology,USB-A1HSW6,ED2989-ND,,,,
"J15, J16, J16",3,ED2580-ND,On Shore Technology,OSTTA024163,ED2580-ND,,,,
"J17, J25, J21, J20, J19, J24, J22, J18, J23, J26",10,Terminal block 6 pos side entry,On Shore Technology,OSTTE060104,ED2744-ND,,,,
"J5, J1, J4, J3, J2",5,Terminal block 6 pos top entry,On Shore Technology,OSTTF060161,ED2627-ND,,,,
"J7, J6",1,S9175-ND,Sullins,SBH11-PBPC-D20-ST-BK,S9175-ND,,,,
J8,1,6x1 Header Pin 0.1 Pitch 6posheader,Sullins,PRPC040SAAN-RC,S1011EC-40-ND,,,,
"J9, J11",2,S7038-ND,Sullins,PPPC051LFBN-RC,S7038-ND,,,,
R1,1,Resistor 4.7K 1/4 Watt,Stackpole Electronics,CF14JT4K70,CF14JT4K70CT-ND,,,,
R2,1,Resistor 10K 1/2 Watt,Stackpole Electronics,CFM12JT10K0,S10KHCT-ND,,,,
"R7, R9, R5, R3",4,Resistor 22K 1/4 Watt,Stackpole Electronics,CF14JT22K0,CF14JT22K0CT-ND,,,,
"R8, R10, R6, R4",4,Resistor 10K 1/4 Watt,Stackpole Electronics,CF14JT10K0,CF14JT10K0CT-ND,,,,
"RC4, RC2, RC1, RC3, RC5",5,Connector Header socket 20 2x10,Sullins,PPPC102LFBN-RC,S6106-ND,,,,
"U2, U1",2,LM358-N,Texas Instruments,LM358P,296-1395-5-ND,595LM358P,,,
"U2, U1",2,,ASSMANN WSW Components,A 08-LC-TT,AE9986-ND,,6742435,,

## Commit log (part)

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2023-01-23 Adding some pin number hints to footprint silkscreens
2023-01-24 Updating resistor values for u5
2023-01-25 deleting some todos
2023-01-29 adding some notes from thursday convo
2023-01-30 Updating annotations
2023-02-17 progress on new boards layout
2023-02-22 Updating 3d model links again, and adding arduino connector 3d model
2023-02-23 Updated mounting holes for both motor board -> rover body and brain board -> motor board
2023-02-26 layout pretty much done
2023-03-01 Started routing motor lines
2023-03-01 More routing updates to motor board
2023-03-04 fix PCA 3d model link
2023-03-05 progress on brain board
2023-03-07 updating spacing of power connectors for ease of access
2023-03-12 updating trace thicknesses for J20 and J30
2023-03-12 thickening plane connector traces in key spots
2023-03-12 update Batt+/- and switch+/-
2023-03-12 lots of silkscreen updates
2023-03-19 Final commit (hopefully) for v2.0.1 before gerbers
2023-03-19 adding gerbers for v2.0.1
2023-03-20 Update pcb to show traces by default
2023-04-04 Build site with MkDocs
    Closes #317
2023-05-01 update transistors footprints
2023-05-01 flip footprint for j16,j17,j18
2023-05-01 add gerbers for v2.0.2
2023-05-07 Create GH action for parsing parts lists
2023-05-07 Only run on pull_request (or on direct push to master,v2) so that the commit gets added directly to the PR
2023-05-07 Generated by GitHub Actions (Parse parts lists / generate_md)
    https://github.com/nasa-jpl/open-source-rover/actions/runs/4905392732
2023-05-07 Generated by GitHub Actions (Parse parts lists / generate_md)
    https://github.com/nasa-jpl/open-source-rover/actions/runs/4905401809
2023-05-13 Generated by GitHub Actions (Parse parts lists / generate_md)
    https://github.com/nasa-jpl/open-source-rover/actions/runs/4964113615
2023-06-01 Clean up main readme a bit
2023-06-01 Add in progress note
2023-06-26 Add body plate parts and files
2023-06-26 Fix commas in parts list
2023-06-26 Generated by GitHub Actions (Parse parts lists / generate_md)
    https://github.com/nasa-jpl/open-source-rover/actions/runs/5373560955
2023-07-06 fix csv
2023-07-10 Add a bunch of images and update readme with rover pics
2023-07-15 Add screws, nuts, washers
2023-07-17 Add extra part list
2023-07-17 Round total cost, nb wheel pairs -> 3
2023-07-25 Write majority of the wiring diagram. Missing some images
2023-07-25 cabling -> wiring
2023-07-25 Rename all the arduino "sheild" files to "shield"
2023-07-26 replace main readme image with rover with bigger wheels
2023-07-26 Mechanical readme docs, wiring hints
2023-07-27 Add many extra parts
2023-07-27 Add a line break to parts list readme
2023-07-27 Generated by GitHub Actions (Parse parts lists / generate_md)
    https://github.com/nasa-jpl/open-source-rover/actions/runs/5684541520
2023-07-27 Add extra line break
2023-07-28 Changed Extra_parts.md
    Added the parts to extra_parts.md instead and also documented quick instruction on adding/replacing parts
2023-07-28 Update parts_list/extra_parts.md
    spacing
2023-07-28 Revert "Merge branch 'v2' of https://github.com/BaeHenryS/open-source-rover into v2"
    This reverts commit 47249582070f571f29218171b8c73f8f5f29935a, reversing
    changes made to 8829a77f3f454f5b3ab71cf3258acceaa93194da.
2023-07-28 Removed Wire Links for Now
2023-07-30 dashes to asterisks
2023-07-30 Remove integration folder, docu for mech integration, added images
2023-08-02 Removing old v1 files
2023-08-09 Formatting changes for clarity
2023-08-30 Move pcb readme to pcb folder, add instructions for configuring roboclaws
2023-09-12 Add link to youtube video showing OSRv2 roving around
2023-09-15 Update README.md
    adding https:// to www.gobilda.com to avoid error 404
2023-09-18 Generated by GitHub Actions (Parse parts lists / generate_md)
    https://github.com/nasa-jpl/open-source-rover/actions/runs/6228343575
2023-09-26 Generated by GitHub Actions (Parse parts lists / generate_md)
    https://github.com/nasa-jpl/open-source-rover/actions/runs/6317263468
2023-10-05 Only need 4x 41-hole beams iso 6x
    closes #421
2023-10-06 Add rev 4 of the body plates, move instructions for laser cutting to extra_parts readme in parts list
2023-10-06 Move docu to laser cut parts readme, add image showing sendcutsend cart
2023-10-06 Generated by GitHub Actions (Parse parts lists / generate_md)
    https://github.com/nasa-jpl/open-source-rover/actions/runs/6435807995
2023-10-06 Generated by GitHub Actions (Parse parts lists / generate_md)
    https://github.com/nasa-jpl/open-source-rover/actions/runs/6435859472
2023-10-16 Add OSHW certification
2023-10-25 Migrate to `.readthedocs.yaml` configuration file
    As of 2023-09-25 Read the Docs require a `.readthedocs.yaml`
    configuration file.
    See https://blog.readthedocs.com/migrate-configuration-v2/
2023-10-27 Add Raf the Rover to builder's page
2023-11-03 Added rest of harness YAMLs Added harness images Added harness generation scripts (Windows and Linux)
2023-11-07 Added short blurb on generating the WireViz diagrams
2023-11-07 Fix nav link to PCB assembly
2023-11-19 Generated by GitHub Actions (Parse parts lists / generate_md)
    https://github.com/nasa-jpl/open-source-rover/actions/runs/6918161495
2023-11-19 Generated by GitHub Actions (Parse parts lists / generate_md)
    https://github.com/nasa-jpl/open-source-rover/actions/runs/6918910527
2023-12-07 Create demofile
2024-01-13 Generated by GitHub Actions (Parse parts lists / generate_md)
    https://github.com/nasa-jpl/open-source-rover/actions/runs/7510058988
2024-02-04 adding BOM v2.0.3 file based on https://docs.google.com/spreadsheets/d/1Z011-4hdfSKOZROEwKTmGs-w_xfm9FzWOGzqSnaTu4w/edit#gid=1688553179
2024-02-04 update bom name and path
2024-02-05 remove bom xlsx and update some of the todos in the readme
2024-02-05 make readme md
2024-02-08 fix refs to 277-14404-ND.step 3d model in layout
2024-02-08 add schematics, layout diagrams, and images for v2.0.3
2024-02-18 Improve instructions for rocker-bogie assemblies, add more pictures
2024-02-18 Specify 14V iso 12V batter and explain why
2024-02-23 Added Bobert to builders' gallery
2024-02-24 Generated by GitHub Actions (Parse parts lists / generate_md)
    https://github.com/nasa-jpl/open-source-rover/actions/runs/8027283258
2024-03-07 Add wheel screws to screws.md
2024-03-21 Adding samwise to builders gallery
2024-04-06 Fixes/prunes broken nav links.
2024-04-07 Reword discount Gobilda
2024-04-11 some more small updates after readthru
2024-04-11 Generated by GitHub Actions (Parse parts lists / generate_md)
    https://github.com/nasa-jpl/open-source-rover/actions/runs/8652994695
2024-04-17 Adds links for Molex 6-pin connectors to parts list.
2024-04-21 Generated by GitHub Actions (Parse parts lists / generate_md)
    https://github.com/nasa-jpl/open-source-rover/actions/runs/8775628159
2024-05-13 Image Modification
2024-06-22 Update the build instructions to default to the wasteland wheels, update screws
2024-09-24 Clarified instructions for step 4.5
2024-11-21 Generated by GitHub Actions (Parse parts lists / generate_md)
    https://github.com/nasa-jpl/open-source-rover/actions/runs/11945816781
2024-11-28 removed duplicate mention of the PCA9685 corner motor driver
2024-12-02 Generated by GitHub Actions (Parse parts lists / generate_md)
    https://github.com/nasa-jpl/open-source-rover/actions/runs/12112439803
2024-12-10 re-arranging some content to make it read more smoothly
2024-12-10 fixed some typos and bad paths
2024-12-13 added image of rocker bogie sleeves
2024-12-17 added another image and clarifying language for the power header PCB assembly steps
2024-12-31 added a paragraph about how to power an RPi 5
2025-01-03 Generated by GitHub Actions (Parse parts lists / generate_md)
    https://github.com/Achllle/open-source-rover/actions/runs/12601976863
2025-01-07 Adjusted language
2025-02-04 added description and files for scout rover
2025-03-03 Add rpi5 option, price disclaimer
2025-03-07 Added note about continuity testing beep in Step 3.4
2025-03-13 fixed a few typos
2025-03-17 reworked the directory struction so that it is now expansion/mast/
2025-04-23 Bump jinja2 from 3.0.3 to 3.1.6
    Bumps [jinja2](https://github.com/pallets/jinja) from 3.0.3 to 3.1.6.
    - [Release notes](https://github.com/pallets/jinja/releases)
    - [Changelog](https://github.com/pallets/jinja/blob/main/CHANGES.rst)
    - [Commits](https://github.com/pallets/jinja/compare/3.0.3...3.1.6)
    ---
    updated-dependencies:
2025-05-20 Warning about updating roboclaw firmware (#514)
2025-05-26 Revert "Warning about updating roboclaw firmware (#514)" (#515)
    This reverts commit f899657f5b133e904bfa64f9660d936abb34214a.
2025-06-05 Update README.md
    Fixing error with Resilience Add
2025-06-05 Update README.md
    Fixing Resilience add. File extensions capitalized, changing background.
2025-06-05 Delete examples/images/Resilience/Resilience_Ocean.PNG
    Deleting png files and replacing with jpegs
2025-06-05 Update README.md
    Fixing a few things in Resilience writeup
2025-06-05 Delete examples/images/Resilience/Resilience_at_School.jpeg
    Deleting picture.
2025-06-18 Bump jinja2 from 3.0.3 to 3.1.6 (#512)
    Bumps [jinja2](https://github.com/pallets/jinja) from 3.0.3 to 3.1.6.
    - [Release notes](https://github.com/pallets/jinja/releases)
    - [Changelog](https://github.com/pallets/jinja/blob/main/CHANGES.rst)
    - [Commits](https://github.com/pallets/jinja/compare/3.0.3...3.1.6)
    ---
    updated-dependencies:
2025-07-15 Added `Calibrate Velocity Settings` section to PCB README
2025-07-16 updating spacing for consistency
2025-07-16 Added Velocity Calibration steps to motor setup (#519)
    * Added `Calibrate Velocity Settings` section to PCB README
    * revised description of autotunning process
    * updating spacing for consistency
    * changed clamping mount to bore hub and added link
    ---------
2025-09-24 added testing of INA260
2025-09-24 updated PCA9685 instructions
2025-09-27 Improve build documentation (#523)
    * added INA260 details
    * added testing of INA260
    * Added details of testing the INA260 in the README
    * updated PCA9685 instructions
    * typo
    * specify wire length for roboclaws
2025-09-29 use updated image
2025-09-29 fixing link format
2025-09-29 easier to trim C32 if installed before J27-29.
2025-10-07 typos
2025-10-07 fix url
2025-10-08 revert image change
2025-10-13 add todo, change color on image (box to hide nuts)
2025-10-13 renumber figs, remove duplicate
2025-10-14 improving brain board documentation (#524)
    * added INA260 details
    * added testing of INA260
    * Added details of testing the INA260 in the README
    * updated PCA9685 instructions
    * typo
    * specify wire length for roboclaws
2025-10-17 notch corner goRail
2025-10-22 typos, updated CAD link
2025-10-31 more detail on grommets, wiring assembly order
2025-10-31 Fix typo in README.md for wheel assembly instructions
2025-11-03 Update mechanical/wheel_assembly/README.md
    depersonalize wording
2025-11-04 major restructuring of rb wiring instructions, more pics
2025-11-20 adding my rover to the OSR gallery
2025-12-01 update ref to control arm assembly image
2025-12-02 improve body build documentation & images - increase nut count (#527)
    * improved body and hinge pictures and text
    * improved body description and assembly images. Increased nut count.
    * add todo, change color on image (box to hide nuts)
    * update body panel image
    * Update mechanical/body/README.md
    typo
2025-12-25 Bump pymdown-extensions from 10.0 to 10.16.1
    Bumps [pymdown-extensions](https://github.com/facelessuser/pymdown-extensions) from 10.0 to 10.16.1.
    - [Release notes](https://github.com/facelessuser/pymdown-extensions/releases)
    - [Commits](https://github.com/facelessuser/pymdown-extensions/compare/10.0...10.16.1)
    ---
    updated-dependencies:
    - dependency-name: pymdown-extensions
2026-02-19 docs(pcb): clarify female/male header terminology and BOM mapping
2026-03-25 Update link to battery charger
2026-03-27 ci: Throw clear error when autogenerated parts list is not updated
    Before, the int128/update-generated-files-action would attempt to push, but github doesn't allow the action to run on forks
    for security reasons. The action will still work on direct pushes
